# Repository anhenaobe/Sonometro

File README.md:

# Sonómetro IEPE de un canal

Prototipo académico de sonómetro digital con micrófono IEPE externo, a desarrollar del **24 de octubre al 24 de noviembre de 2026**. Este repositorio es independiente de VibrationDAQ.

## Alcance

Adquirir un canal, transferir muestras al PC y visualizar señal temporal, RMS y FFT en Python; después calcular presión y SPL con calibración documentada. No se declara clase metrológica, cumplimiento normativo ni rendimiento acústico validado.

```text
Micrófono IEPE externo → corriente constante → protección y acoplamiento AC
→ acondicionamiento analógico → ADC de audio → STM32 → USB → Python/PC
```

**PROVISIONAL:** LT3092 y PCM1808. **STM32L432KC es la MCU decidida**, con NUCLEO-L432KC para prototipo y PCB convencional como implementación final; F446RE se conserva como antecedente. Hay [firmware STM32Cube HAL](firmware/README.md) compilable para ADC interno de 12 bits + temporizador + DMA y capturas por bloques vía ST-LINK VCP, y [herramienta Python](software/README.md). La adquisición física sigue OPEN; SAI/PCM1808 requiere implementación y validación.

**Revisión para el 5/11:** [propuesta breve en PDF](output/pdf/propuesta-revisada-iepe.pdf), [informe de cálculos y decisiones](docs/revision-arquitectura.md) y [simulaciones reproducibles con gráficas](hardware/revision/README.md). Compara fuentes, filtros, referencias y cuatro arquitecturas ADC. Recomendación A3 condicionada a protección y pruebas; no autoriza fabricación todavía. Plazo actualizado de entrega: aproximadamente **25/11/2026**.

La [propuesta analógica](docs/analog-front-end.md) compara tres arquitecturas y entrega cálculos/netlists/simulaciones reproducibles. El contrato de protección, polarización y carga del acoplamiento previo sigue pendiente de cierre entre equipos.

Referencia de sensor: ROGA RG-50. Los datos aportados de la unidad son 55,6 mV/Pa, bias de 12,5 V y corriente indicada de 2,8 mA; su aplicabilidad debe verificarse antes de conectarla. La prueba de 2,4/2,8/4 mA empieza con cargas de prueba, sin micrófono.

## Cómo comenzar

1. Revisar [decisiones y fuentes oficiales](docs/decisions.md), identificar el micrófono y confirmar sus límites/certificado.
2. Asignar personas a los tres roles del [plan](docs/plan.md), comprobar existencias reales y completar la [BOM](hardware/bom.csv).
3. Ejecutar las pruebas separadas de corriente y adquisición del [protocolo](tests/README.md) para el 28 de octubre. Conservar datos crudos y configuración, incluidos fallos.
4. Implementar primero una captura reproducible en [firmware](firmware/README.md) y [software](software/README.md); integrar el sensor solo tras aprobar las verificaciones eléctricas.

Estados: **CONFIRMED** = evidencia o decisión explícita con alcance indicado; **PROVISIONAL** = candidato o meta revisable; **OPEN** = falta decidir/verificar. Ningún estado de selección equivale a prueba física aprobada.

La licencia existente se conserva en [LICENSE](LICENSE). Las referencias externas se enlazan y atribuyen en decisiones; no se incluyen copias de circuitos ni archivos de terceros.

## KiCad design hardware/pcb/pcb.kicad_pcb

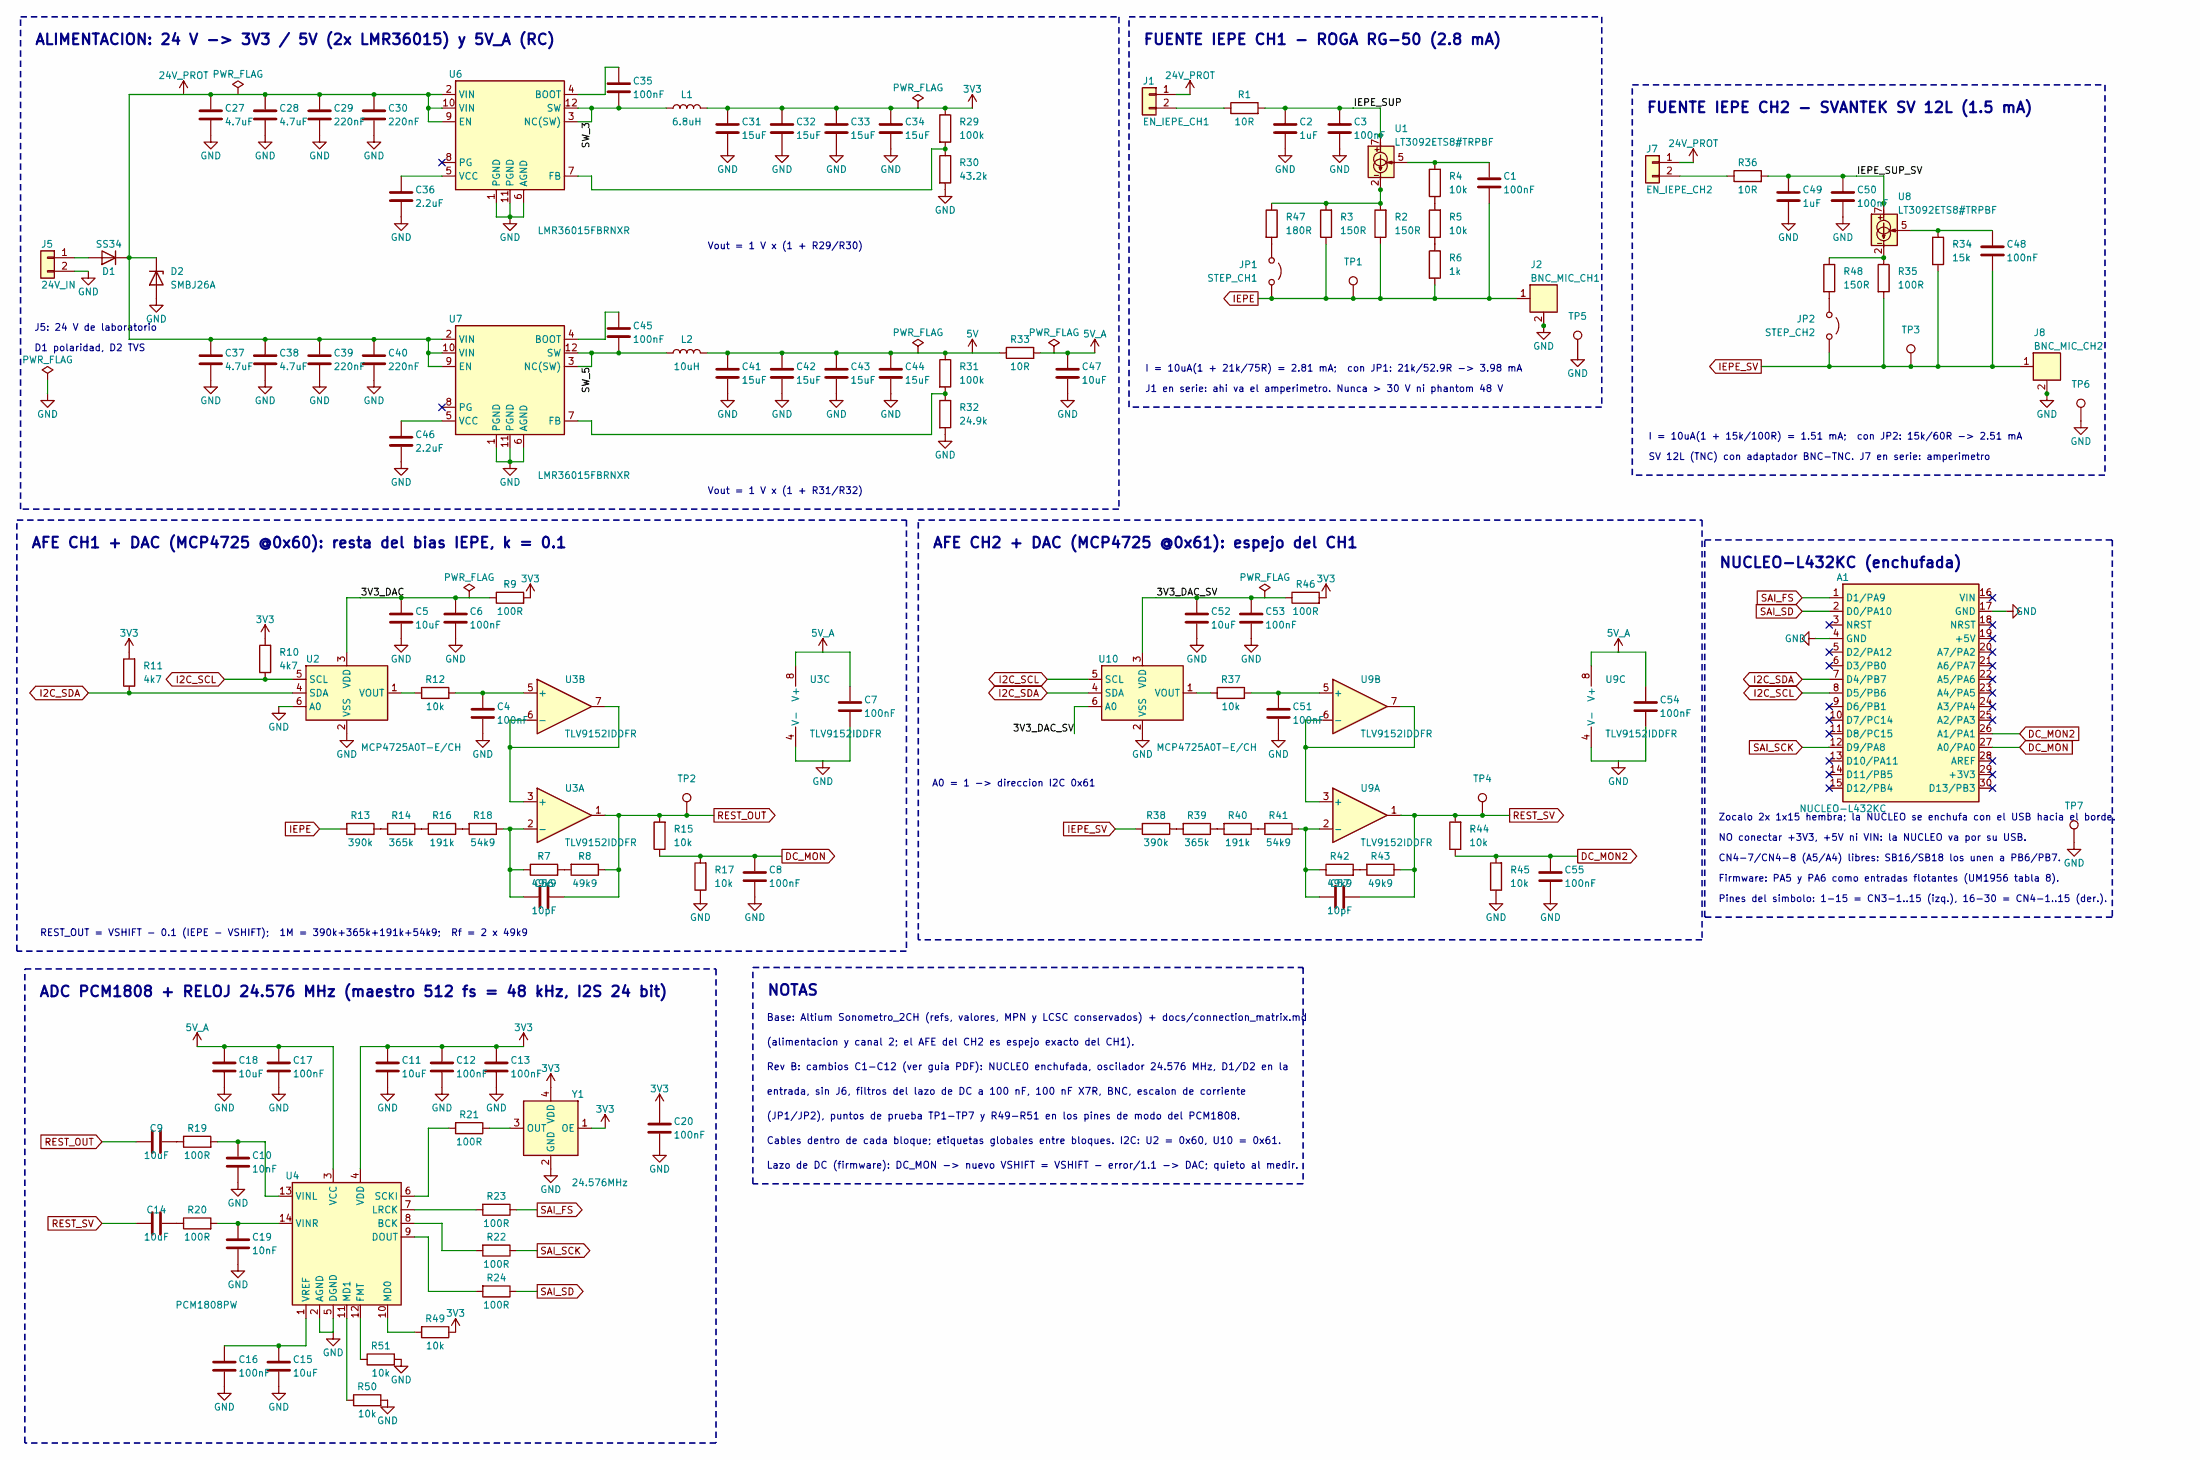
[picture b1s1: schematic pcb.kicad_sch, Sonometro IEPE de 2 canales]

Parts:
A1: NUCLEO-L432KC; NUCLEO-32_Socket_2x15_P2.54mm_Row15.24mm; MPN KH-2.54FH-1X15P-H8.5 (x2) + NUCLEO-L432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; LCSC C2932676 (x2)
C1, C3, C4, C6, C7, C8, C12, C13, C16, C17, C20, C35, C45, C48, C50, C51, C53, C54, C55: 100nF; C_0603_1608Metric; MPN CC0603KRX7R9BB104; LCSC C14663
C2, C49: 1uF; C_0603_1608Metric; MPN CL10A105KB8NNNC; LCSC C15849
C5, C9, C11, C14, C15, C18, C47, C52: 10uF; C_0603_1608Metric; MPN CL10A106KP8NNNC; LCSC C19702
C10, C19: 10nF; C_0402_1005Metric_JLC; MPN CL05B103KB5NNNC; LCSC C15195
C27, C28, C37, C38: 4.7uF; C_2220_5750Metric; MPN FS55X475K101EGG; LCSC C153031
C29, C30, C39, C40: 220nF; C_0805_2012Metric; MPN C0805C224K1RACTU; LCSC C2167405
C31, C32, C33, C34, C41, C42, C43, C44: 15uF; C_1210_3225Metric; MPN C3225X7R1C156MT000N; LCSC C694469
C36, C46: 2.2uF; C_0805_2012Metric; MPN CC0805KKX7R9BB225; LCSC C125847
C56, C57: 10pF; C_0603_1608Metric; MPN CL10C100JB8NNNC; LCSC C1634
D1: SS34; D_SMA; MPN SS34; LCSC C8678
D2: SMBJ26A; D_SMB; MPN SMBJ26A; LCSC C123820
J1: EN_IEPE_CH1; TerminalBlock_MaiXu_MX126-5.0-02P_1x02_P5.00mm_Borde; MPN JL126-50002G01; LCSC C394556
J2: BNC_MIC_CH1; BNC_Kinghelm_KH-BNC75-3511_Horizontal; MPN KH-BNC75-3511; LCSC C2837588
J5: 24V_IN; TerminalBlock_MaiXu_MX126-5.0-02P_1x02_P5.00mm_Borde; MPN JL126-50002G01; LCSC C394556
J7: EN_IEPE_CH2; TerminalBlock_MaiXu_MX126-5.0-02P_1x02_P5.00mm_Borde; MPN JL126-50002G01; LCSC C394556
J8: BNC_MIC_CH2; BNC_Kinghelm_KH-BNC75-3511_Horizontal; MPN KH-BNC75-3511; LCSC C2837588
JP1: STEP_CH1; PinHeader_1x02_P2.54mm_Vertical; MPN Header 1x2 2.54 + jumper
JP2: STEP_CH2; PinHeader_1x02_P2.54mm_Vertical; MPN Header 1x2 2.54 + jumper
L1: 6.8uH; L_Coilcraft_XAL4030-XXX; MPN XAL4030-682MEC; LCSC C3040663
L2: 10uH; L_Coilcraft_XAL4040-XXX; MPN XAL4040-103MEC; LCSC C5144883
R1, R36: 10R; R_0402_1005Metric_JLC; MPN 0402WGF100JTCE; LCSC C25077
R2, R3, R48: 150R; R_0603_1608Metric; MPN 0603WAF1500T5E; LCSC C22808
R4, R5, R12, R15, R17, R37, R44, R45, R49, R50, R51: 10k; R_0603_1608Metric; MPN 0603WAF1002T5E; LCSC C25804
R6: 1k; R_0603_1608Metric; MPN 0603WAF1001T5E; LCSC C21190
R7, R8, R42, R43: 49k9; R_0603_1608Metric; MPN 0603WAF4992T5E; LCSC C23184
R9, R19, R20, R21, R22, R23, R24, R35, R46: 100R; R_0603_1608Metric; MPN 0603WAF1000T5E; LCSC C22775
R10, R11: 4k7; R_0603_1608Metric; MPN 0603WAF4701T5E; LCSC C23162
R13, R38: 390k; R_0603_1608Metric; MPN RC0603FR-07390KL; LCSC C137735
R14, R39: 365k; R_0603_1608Metric; MPN RC0603FR-07365KL; LCSC C185336
R16, R40: 191k; R_0603_1608Metric; MPN AC0603FR-07191KL; LCSC C227635
R18, R41: 54k9; R_0603_1608Metric; MPN RC0603FR-0754K9L; LCSC C185321
R29, R31: 100k; R_0603_1608Metric; MPN 0603WAF1003T5E; LCSC C25803
R30: 43.2k; R_0603_1608Metric; MPN RC0603FR-0743K2L; LCSC C137720
R32: 24.9k; R_0603_1608Metric; MPN RC0603FR-0724K9L; LCSC C137761
R33: 10R; R_0603_1608Metric; MPN 0603WAF100JT5E; LCSC C22859
R34: 15k; R_0603_1608Metric; MPN 0603WAF1502T5E; LCSC C22809
R47: 180R; R_0603_1608Metric; MPN 0603WAF1800T5E; LCSC C22828
TP1: TP_IEPE; TestPoint_THTPad_D2.0mm_Drill1.0mm_JLC
TP2: TP_REST_OUT; TestPoint_THTPad_D2.0mm_Drill1.0mm_JLC
TP3: TP_IEPE_SV; TestPoint_THTPad_D2.0mm_Drill1.0mm_JLC
TP4: TP_REST_SV; TestPoint_THTPad_D2.0mm_Drill1.0mm_JLC
TP5, TP6, TP7: TP_GND; TestPoint_THTPad_D2.0mm_Drill1.0mm_JLC
U1, U8: LT3092ETS8#TRPBF; TSOT-23-8_Pad0.40x1.22mm_P0.65mm_ADI; MPN LT3092ETS8#TRPBF; LCSC C462641
U2, U10: MCP4725A0T-E/CH; SOT-23-6; MPN MCP4725A0T-E/CH; LCSC C144198
U3, U9: TLV9152IDDFR; TSOT-23-8_Pad0.40x1.22mm_P0.65mm_ADI; MPN TLV9152IDDFR; LCSC C2861011
U4: PCM1808PW; TSSOP-14_4.4x5mm_P0.65mm; MPN PCM1808PWR; LCSC C55513
U6, U7: LMR36015FBRNXR; Texas_RNX0012A_VQFN-HR-12_2x3mm_P0.5mm; MPN LMR36015FBRNXR; LCSC C1850339
Y1: 24.576MHz; Oscillator_YXC_SMD3225-4Pin_3.2x2.5mm; MPN O322524576MEEA4SC; LCSC C27869

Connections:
3V3: C11.1, C12.1, C13.1, C20.1, C31.1, C32.1, C33.1, C34.1, L1.2, R9.2, R10.2, R11.2, R29.1, R46.2, R49.1, U4.4 (VDD), Y1.1 (OE), Y1.4 (VDD)
5V: C41.1, C42.1, C43.1, C44.1, L2.2, R31.1, R33.1
5V_A: C7.2, C17.1, C18.1, C47.1, C54.2, R33.2, U3.8 (V+), U4.3 (VCC), U9.8 (V+)
24V_PROT: C27.1, C28.1, C29.1, C30.1, C37.1, C38.1, C39.1, C40.1, D1.1 (K), D2.1 (K), J1.1, J7.1, U6.2 (VIN), U6.9 (EN), U6.10 (VIN), U7.2 (VIN), U7.9 (EN), U7.10 (VIN)
/3V3_DAC: C5.1, C6.1, R9.1, U2.3 (VDD)
/3V3_DAC_SV: C52.1, C53.1, R46.1, U10.3 (VDD), U10.6 (A0)
/IEPE_SUP: C2.1, C3.1, R1.2, U1.7, U1.8
/IEPE_SUP_SV: C49.1, C50.1, R36.2, U8.7, U8.8
/SW_3: C35.2, L1.1, U6.3 (NC(SW)), U6.12 (SW)
/SW_5: C45.2, L2.1, U7.3 (NC(SW)), U7.12 (SW)
DC_MON: A1.27 (A0/PA0), C8.1, R15.1, R17.2
DC_MON2: A1.26 (A1/PA1), C55.1, R44.1, R45.2
GND: A1.4 (GND), A1.17 (GND), C2.2, C3.2, C4.2, C5.2, C6.2, C7.1, C8.2, C10.2, C11.2, C12.2, C13.2, C15.2, C16.2, C17.2, C18.2, C19.2, C20.2, C27.2, C28.2, C29.2, C30.2, C31.2, C32.2, C33.2, C34.2, C36.2, C37.2, C38.2, C39.2, C40.2, C41.2, C42.2, C43.2, C44.2, C46.2, C47.2, C49.2, C50.2, C51.2, C52.2, C53.2, C54.1, C55.2, D2.2 (A), J2.2 (SHIELD), J2.3 (SHIELD), J2.4 (SHIELD), J5.2, J8.2 (SHIELD), J8.3 (SHIELD), J8.4 (SHIELD), R17.1, R30.2, R32.2, R45.1, R50.2, R51.2, TP5.1, TP6.1, TP7.1, U2.2 (VSS), U2.6 (A0), U3.4 (V-), U4.2 (AGND), U4.5 (DGND), U6.1 (PGND), U6.6 (AGND), U6.11 (PGND), U7.1 (PGND), U7.6 (AGND), U7.11 (PGND), U9.4 (V-), U10.2 (VSS), Y1.2 (GND)
I2C_SCL: A1.8 (D5/PB6), R10.1, U2.5 (SCL), U10.5 (SCL)
I2C_SDA: A1.7 (D4/PB7), R11.1, U2.4 (SDA), U10.4 (SDA)
IEPE: C1.2, J2.1 (SIG), JP1.2 (B), R2.1, R3.1, R6.2, R13.2, TP1.1
IEPE_SV: C48.2, J8.1 (SIG), JP2.2 (B), R34.2, R35.2, R38.2, TP3.1
unnamed: C1.1, R4.2, U1.5
unnamed: C9.2, R19.1
unnamed: C14.2, R20.1
unnamed: C48.1, R34.1, U8.5
unnamed: D1.2 (A), J5.1
unnamed: J1.2, R1.1
unnamed: J7.2, R36.1
unnamed: JP1.1 (A), R47.2
unnamed: JP2.1 (A), R48.2
unnamed: R2.2, R3.2, R47.1, U1.2, U1.3, U1.4
unnamed: R4.1, R5.2
unnamed: R5.1, R6.1
unnamed: R7.2, R8.2
unnamed: R13.1, R14.2
unnamed: R14.1, R16.2
unnamed: R16.1, R18.2
unnamed: R35.1, R48.1, U8.2, U8.3, U8.4
unnamed: R38.1, R39.2
unnamed: R39.1, R40.2
unnamed: R40.1, R41.2
unnamed: R42.2, R43.2
unnamed: R12.1, U2.1 (VOUT)
unnamed: U3.3 (+), U3.6 (-), U3.7
unnamed: C56.1, R7.1, R18.1, U3.2 (-)
unnamed: C4.1, R12.2, U3.5 (+)
unnamed: R22.2, U4.8 (BCK)
unnamed: R24.2, U4.9 (DOUT)
unnamed: R51.1, U4.12 (FMT)
unnamed: R23.2, U4.7 (LRCK)
unnamed: R49.2, U4.10 (MD0)
unnamed: R50.1, U4.11 (MD1)
unnamed: R21.2, U4.6 (SCKI)
unnamed: C10.1, R19.2, U4.13 (VINL)
unnamed: C19.1, R20.2, U4.14 (VINR)
unnamed: C15.1, C16.1, U4.1 (VREF)
unnamed: C35.1, U6.4 (BOOT)
unnamed: R29.2, R30.1, U6.7 (FB)
unnamed: C36.1, U6.5 (VCC)
unnamed: C45.1, U7.4 (BOOT)
unnamed: R31.2, R32.1, U7.7 (FB)
unnamed: C46.1, U7.5 (VCC)
unnamed: U9.3 (+), U9.6 (-), U9.7
unnamed: C57.1, R41.1, R42.1, U9.2 (-)
unnamed: C51.1, R37.2, U9.5 (+)
unnamed: R37.1, U10.1 (VOUT)
unnamed: R21.1, Y1.3 (OUT)
REST_OUT: C9.1, C56.2, R8.1, R15.2, TP2.1, U3.1
REST_SV: C14.1, C57.2, R43.1, R44.2, TP4.1, U9.1
SAI_FS: A1.1 (D1/PA9), R23.1
SAI_SCK: A1.12 (D9/PA8), R22.1
SAI_SD: A1.2 (D0/PA10), R24.1

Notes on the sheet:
Vout = 1 V x (1 + R29/R30)
Vout = 1 V x (1 + R31/R32)
J5: 24 V de laboratorio
D1 polaridad, D2 TVS
ALIMENTACION: 24 V -> 3V3 / 5V (2x LMR36015) y 5V_A (RC)
I = 10uA(1 + 21k/75R) = 2.81 mA; con JP1: 21k/52.9R -> 3.98 mA
J1 en serie: ahi va el amperimetro. Nunca > 30 V ni phantom 48 V
FUENTE IEPE CH1 - ROGA RG-50 (2.8 mA)
I = 10uA(1 + 15k/100R) = 1.51 mA; con JP2: 15k/60R -> 2.51 mA
SV 12L (TNC) con adaptador BNC-TNC. J7 en serie: amperimetro
FUENTE IEPE CH2 - SVANTEK SV 12L (1.5 mA)
REST_OUT = VSHIFT - 0.1 (IEPE - VSHIFT); 1M = 390k+365k+191k+54k9; Rf = 2 x 49k9
AFE CH1 + DAC (MCP4725 @0x60): resta del bias IEPE, k = 0.1
A0 = 1 -> direccion I2C 0x61
AFE CH2 + DAC (MCP4725 @0x61): espejo del CH1
Zocalo 2x 1x15 hembra; la NUCLEO se enchufa con el USB hacia el borde.
NO conectar +3V3, +5V ni VIN: la NUCLEO va por su USB.
CN4-7/CN4-8 (A5/A4) libres: SB16/SB18 los unen a PB6/PB7.
Firmware: PA5 y PA6 como entradas flotantes (UM1956 tabla 8).
Pines del simbolo: 1-15 = CN3-1..15 (izq.), 16-30 = CN4-1..15 (der.).
NUCLEO-L432KC (enchufada)
ADC PCM1808 + RELOJ 24.576 MHz (maestro 512 fs = 48 kHz, I2S 24 bit)
Base: Altium Sonometro_2CH (refs, valores, MPN y LCSC conservados) + docs/connection_matrix.md
(alimentacion y canal 2; el AFE del CH2 es espejo exacto del CH1).
Rev B: cambios C1-C12 (ver guia PDF): NUCLEO enchufada, oscilador 24.576 MHz, D1/D2 en la
entrada, sin J6, filtros del lazo de DC a 100 nF, 100 nF X7R, BNC, escalon de corriente
(JP1/JP2), puntos de prueba TP1-TP7 y R49-R51 en los pines de modo del PCM1808.
Cables dentro de cada bloque; etiquetas globales entre bloques. I2C: U2 = 0x60, U10 = 0x61.
Lazo de DC (firmware): DC_MON -> nuevo VSHIFT = VSHIFT - error/1.1 -> DAC; quieto al medir.
NOTAS

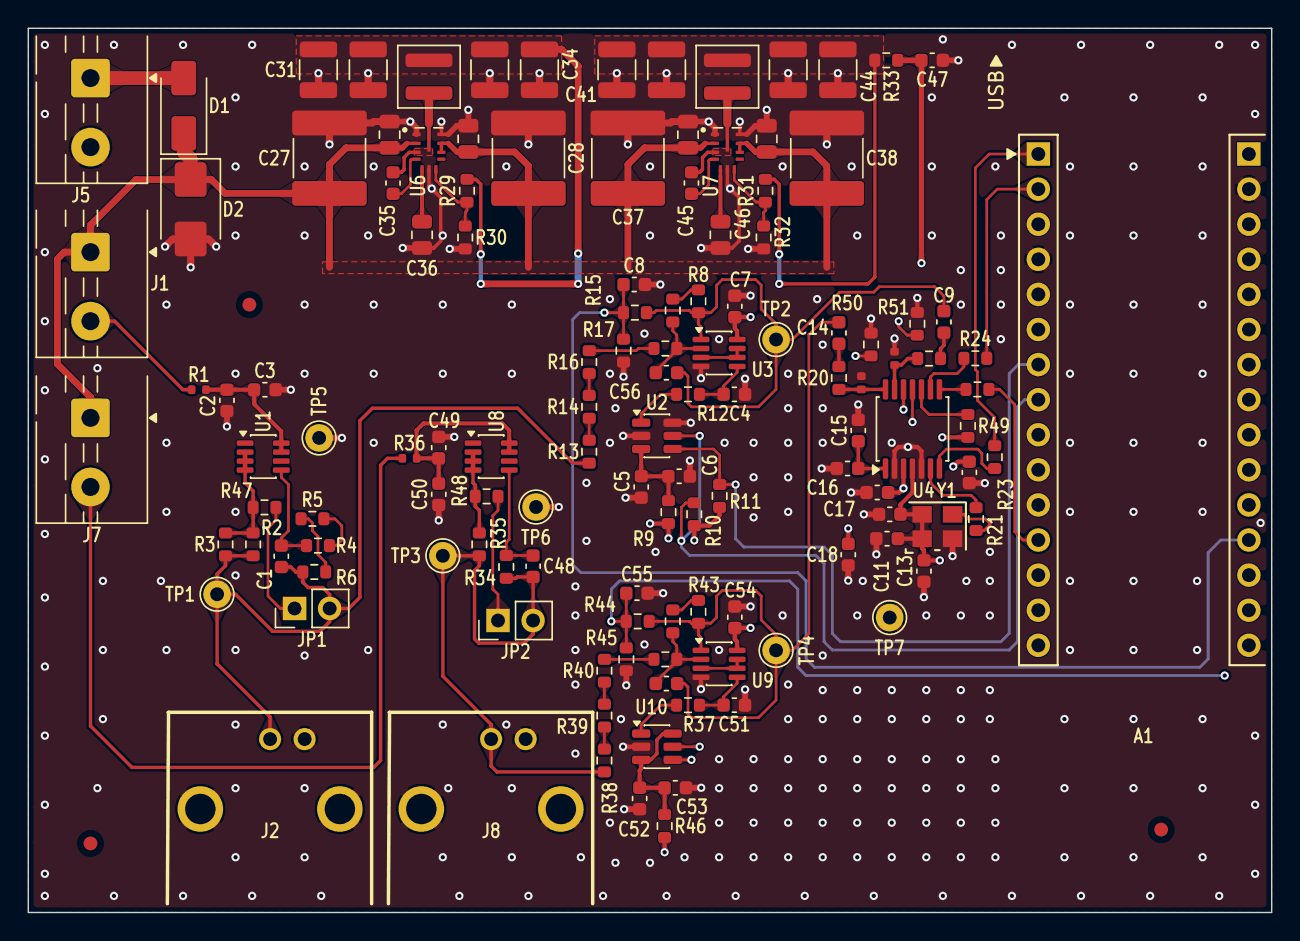
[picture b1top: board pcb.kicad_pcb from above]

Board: 4 copper layers, 90.0 x 64.0 mm, 130 parts (0 on the bottom side), 68 nets.

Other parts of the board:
FID1, FID2, FID3: Fiducial_1mm_Mask2mm

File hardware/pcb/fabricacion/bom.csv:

Comment,Designator,Footprint,LCSC Part Number
100nF,"C1,C3,C4,C6,C7,C8,C12,C13,C16,C17,C20,C35,C45,C48,C50,C51,C53,C54,C55",C_0603_1608Metric,C14663
1uF,"C2,C49",C_0603_1608Metric,C15849
10uF,"C5,C9,C11,C14,C15,C18,C47,C52",C_0603_1608Metric,C19702
10nF,"C10,C19",C_0402_1005Metric_JLC,C15195
4.7uF,"C27,C28,C37,C38",C_2220_5750Metric,C153031
220nF,"C29,C30,C39,C40",C_0805_2012Metric,C2167405
15uF,"C31,C32,C33,C34,C41,C42,C43,C44",C_1210_3225Metric,C694469
2.2uF,"C36,C46",C_0805_2012Metric,C125847
10pF,"C56,C57",C_0603_1608Metric,C1634
SS34,D1,D_SMA,C8678
SMBJ26A,D2,D_SMB,C123820
6.8uH,L1,L_Coilcraft_XAL4030-XXX,C3040663
10uH,L2,L_Coilcraft_XAL4040-XXX,C5144883
10R,"R1,R36",R_0402_1005Metric_JLC,C25077
150R,"R2,R3,R48",R_0603_1608Metric,C22808
10k,"R4,R5,R12,R15,R17,R37,R44,R45,R49,R50,R51",R_0603_1608Metric,C25804
1k,R6,R_0603_1608Metric,C21190
49k9,"R7,R8,R42,R43",R_0603_1608Metric,C23184
100R,"R9,R19,R20,R21,R22,R23,R24,R35,R46",R_0603_1608Metric,C22775
4k7,"R10,R11",R_0603_1608Metric,C23162
390k,"R13,R38",R_0603_1608Metric,C137735
365k,"R14,R39",R_0603_1608Metric,C185336
191k,"R16,R40",R_0603_1608Metric,C227635
54k9,"R18,R41",R_0603_1608Metric,C185321
100k,"R29,R31",R_0603_1608Metric,C25803
43.2k,R30,R_0603_1608Metric,C137720
24.9k,R32,R_0603_1608Metric,C137761
10R,R33,R_0603_1608Metric,C22859
15k,R34,R_0603_1608Metric,C22809
180R,R47,R_0603_1608Metric,C22828
LT3092ETS8#TRPBF,"U1,U8",TSOT-23-8_Pad0.40x1.22mm_P0.65mm_ADI,C462641
MCP4725A0T-E/CH,"U2,U10",SOT-23-6,C144198
TLV9152IDDFR,"U3,U9",TSOT-23-8_Pad0.40x1.22mm_P0.65mm_ADI,C2861011
PCM1808PW,U4,TSSOP-14_4.4x5mm_P0.65mm,C55513
LMR36015FBRNXR,"U6,U7",Texas_RNX0012A_VQFN-HR-12_2x3mm_P0.5mm,C1850339
24.576MHz,Y1,Oscillator_YXC_SMD3225-4Pin_3.2x2.5mm,C27869

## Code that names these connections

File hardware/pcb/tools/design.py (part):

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    {str(n): NUC.get(n) for n in range(1, 31)}, 'KH-2.54FH-1X15P-H8.5 (x2) + NUCLEO-L432KC',
    'C2932676 (x2)',
    'Zocalo 2x 1x15 hembra 2.54 mm a 15.24 mm. Solo GND y senales; NO conectar +3V3, +5V ni VIN. '
    'CN4-7/CN4-8 (A5/A4) quedan libres: SB16/SB18 los unen a PB6/PB7 en la NUCLEO.',
    'cambio C2 (UM1956 tabla 16)')
parts['A1']['mount'] = 'Manual'
change('C2', 'Zócalo para la NUCLEO (A1)',
       'D1/PA9 = SAI_FS (CN3-1), D0/PA10 = SAI_SD (CN3-2), D9/PA8 = SAI_SCK (CN3-12), '
       'D4/PB7 = I2C_SDA (CN3-7), D5/PB6 = I2C_SCL (CN3-8), A0/PA0 = DC_MON (CN4-12), '
       'A1/PA1 = DC_MON2 (CN4-11), GND = CN3-4 y CN4-2. Funciones verificadas en DS11451 '
       '(PA8/9/10 = SAI1_SCK/FS/SD_A AF13; PB6/PB7 = I2C1 AF4).')
# C3: oscilador disponible en JLC, 24.576 MHz -> fs = 48 kHz exactos
y1 = parts['Y1']
y1.update(sym='Sonometro:O322524576MEEA4SC', value='24.576MHz',
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
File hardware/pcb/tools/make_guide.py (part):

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        if net:
            nm = pinname(r, num)
            nets[net].append(f'{r}.{num}' + (f'({nm})' if nm else ''))
LABELLED = {'GND', '3V3', '5V', '5V_A', '24V_PROT', 'IEPE', 'IEPE_SV', 'REST_OUT', 'REST_SV', 'DC_MON', 'DC_MON2',
            'I2C_SCL', 'I2C_SDA', 'SAI_SCK', 'SAI_FS', 'SAI_SD', 'SW_3', 'SW_5', 'IEPE_SUP', 'IEPE_SUP_SV',
            '3V3_DAC', '3V3_DAC_SV'}
net_block = {n: min(block_of[m.split('.')[0]] for m in mem) for n, mem in nets.items()}
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w(r'''Fuente: ST UM1956 Rev 6 (tabla 16 y figura 5) y DS11451 Rev 4 (tablas de funciones alternas).
La NUCLEO se enchufa en dos tiras hembra 1×15 de 2.54 mm separadas 15.24 mm, \textbf{con el USB hacia el
borde superior} de la placa. Solo se usan GND y señales: \textbf{no conectar +3V3, +5V ni VIN} (la
NUCLEO se alimenta por su USB). PA0 (DC\_MON) está libre: el puente SB17, que la uniría al reloj MCO del
ST-LINK, viene abierto de fábrica (UM1956 tabla 6) y \textbf{no hay que soldarlo}. CN4-7/CN4-8 (A5/A4) quedan
libres porque los puentes SB16/SB18 de la
NUCLEO los unen a PB6/PB7; en el firmware PA5 y PA6 van como entradas flotantes.''')
w(r'\par\begin{center}\footnotesize\begin{tabular}{@{}llll|llll@{}}\toprule')
w(r'\textbf{Pin A1} & \textbf{CN3} & \textbf{Nombre} & \textbf{Red} & \textbf{Pin A1} & \textbf{CN4} & '
  r'\textbf{Nombre} & \textbf{Red}\\\midrule')
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    w(f"{a} & CN3-{i + 1} & {esc(pinname('A1', a))} & {esc(na or '—')} & {b} & CN4-{i + 1} & "
      f"{esc(pinname('A1', b))} & {esc(nb or '—')}\\\\")
w(r'\bottomrule\end{tabular}\end{center}')
w(r'''\par Funciones verificadas: PA8/PA9/PA10 = SAI1\_SCK\_A / SAI1\_FS\_A / SAI1\_SD\_A (AF13);
PB6/PB7 = I2C1\_SCL / I2C1\_SDA (AF4); PA0/PA1 = ADC1\_IN5 / ADC1\_IN6. El PCM1808 es el maestro del
I$^2$S (genera BCK y LRCK); el SAI del STM32 recibe como esclavo.''')

# ------------------------------------------------------------------ 7. placement
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
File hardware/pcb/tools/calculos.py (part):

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    # ---------------- separación por tensión
    w('## 7. Separación por tensión')
    w('')
    grupo = {'24V_PROT', 'Net-(D1-A)', '/IEPE_SUP', '/IEPE_SUP_SV', 'Net-(J1-Pin_2)', 'Net-(J7-Pin_2)', 'IEPE',
             'IEPE_SV', '/SW_3', '/SW_5'}
    grupo = {n for n in grupo if n in {s[3] for s in segs} | {p.GetNetname() for fp in b.GetFootprints()
                                                                 for p in fp.Pads()}}
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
